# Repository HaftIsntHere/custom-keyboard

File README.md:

# Custom Keyboard
This is my fully custom keyboard, fitted with a 75% layout, 2 macro keys, a knob and an oled screen!

I made this project as a continuation for the hackpad, and I really wanted to know how building a real keyboard is, not just a macropad. This helped me finally understand how keyboards really work!
 <br>

## BOM

|Item                                                  |Quantity  |Price                                                                                   |Link #                                                                          |
|------------------------------------------------------|----------|----------------------------------------------------------------------------------------|--------------------------------------------------------------------------------|
|INDIVIDUAL ITEMS                                      |          |                                                                                        |                                                                                |
|                                                      |          |                                                                                        |                                                                                |
|Womier Coffee Cat keycaps                             |1         |26.54 USD                                                                               |https://womierkeyboard.com/products/womier-coffee-cat-143?variant=40539585740871|
|Akko V3 Creamy Purple Pro switches                    |90        |33.72 USD                                                                               |https://en.akkogear.com/product/akko-v3-creamy-purple-pro-switch                |
|PCB                                                   |5         |13 + ~15 = 28 USD (can't see shipping estimate right now, it doesnt let me cause of war)|                                                                                |
|                                                      |          |                                                                                        |                                                                                |
|ALIEXPRESS ITEMS                                      |          |                                                                                        |                                                                                |
|                                                      |          |                                                                                        |                                                                                |
|Knob                                                  |1         |3.58 USD                                                                                |https://www.aliexpress.com/item/1005007576522714.html                           |
|OLED Screen 128x32                                    |1         |3.68 USD                                                                                |https://www.aliexpress.com/item/1005007038294972.html                           |
|DO-35 Diodes                                          |100       |1.65 USD                                                                                |https://www.aliexpress.com/item/4000142272546.html                              |
|Hot swap sockets                                      |110       |15.59 USD                                                                               |https://www.aliexpress.com/item/1005007476614771.html                           |
|Stabilizers (4x 2u + 1x 6.25u)                        |4+1       |7.24 USD                                                                                |https://www.aliexpress.com/item/1005006528731543.html                           |
|ESP32 S3 Devkit C1                                    |1         |19.56 USD (including shipping)                                                          |https://www.aliexpress.com/item/1005003979778978.html                           |
|EC11 Rotary Encoder                                   |1         |1.56 USD (including shipping)                                                           |https://www.aliexpress.com/item/1975155185.html                                 |
|M3 Screws                                             |20        |2.54 USD                                                                                |https://www.aliexpress.com/item/32810872544.html                                |
|Poron strips                                          |64        |4.75 USD                                                                                |https://www.aliexpress.com/item/1005003607093794.html                           |
|                                                      |          |                                                                                        |                                                                                |
|AliExpress Total (including their discounts and stuff)| 51.33 USD|                                                                                        |                                                                                |
|                                                      |          |                                                                                        |                                                                                |
|TOTAL                                                 |          |139.59 USD                                                                              |                                                                                |

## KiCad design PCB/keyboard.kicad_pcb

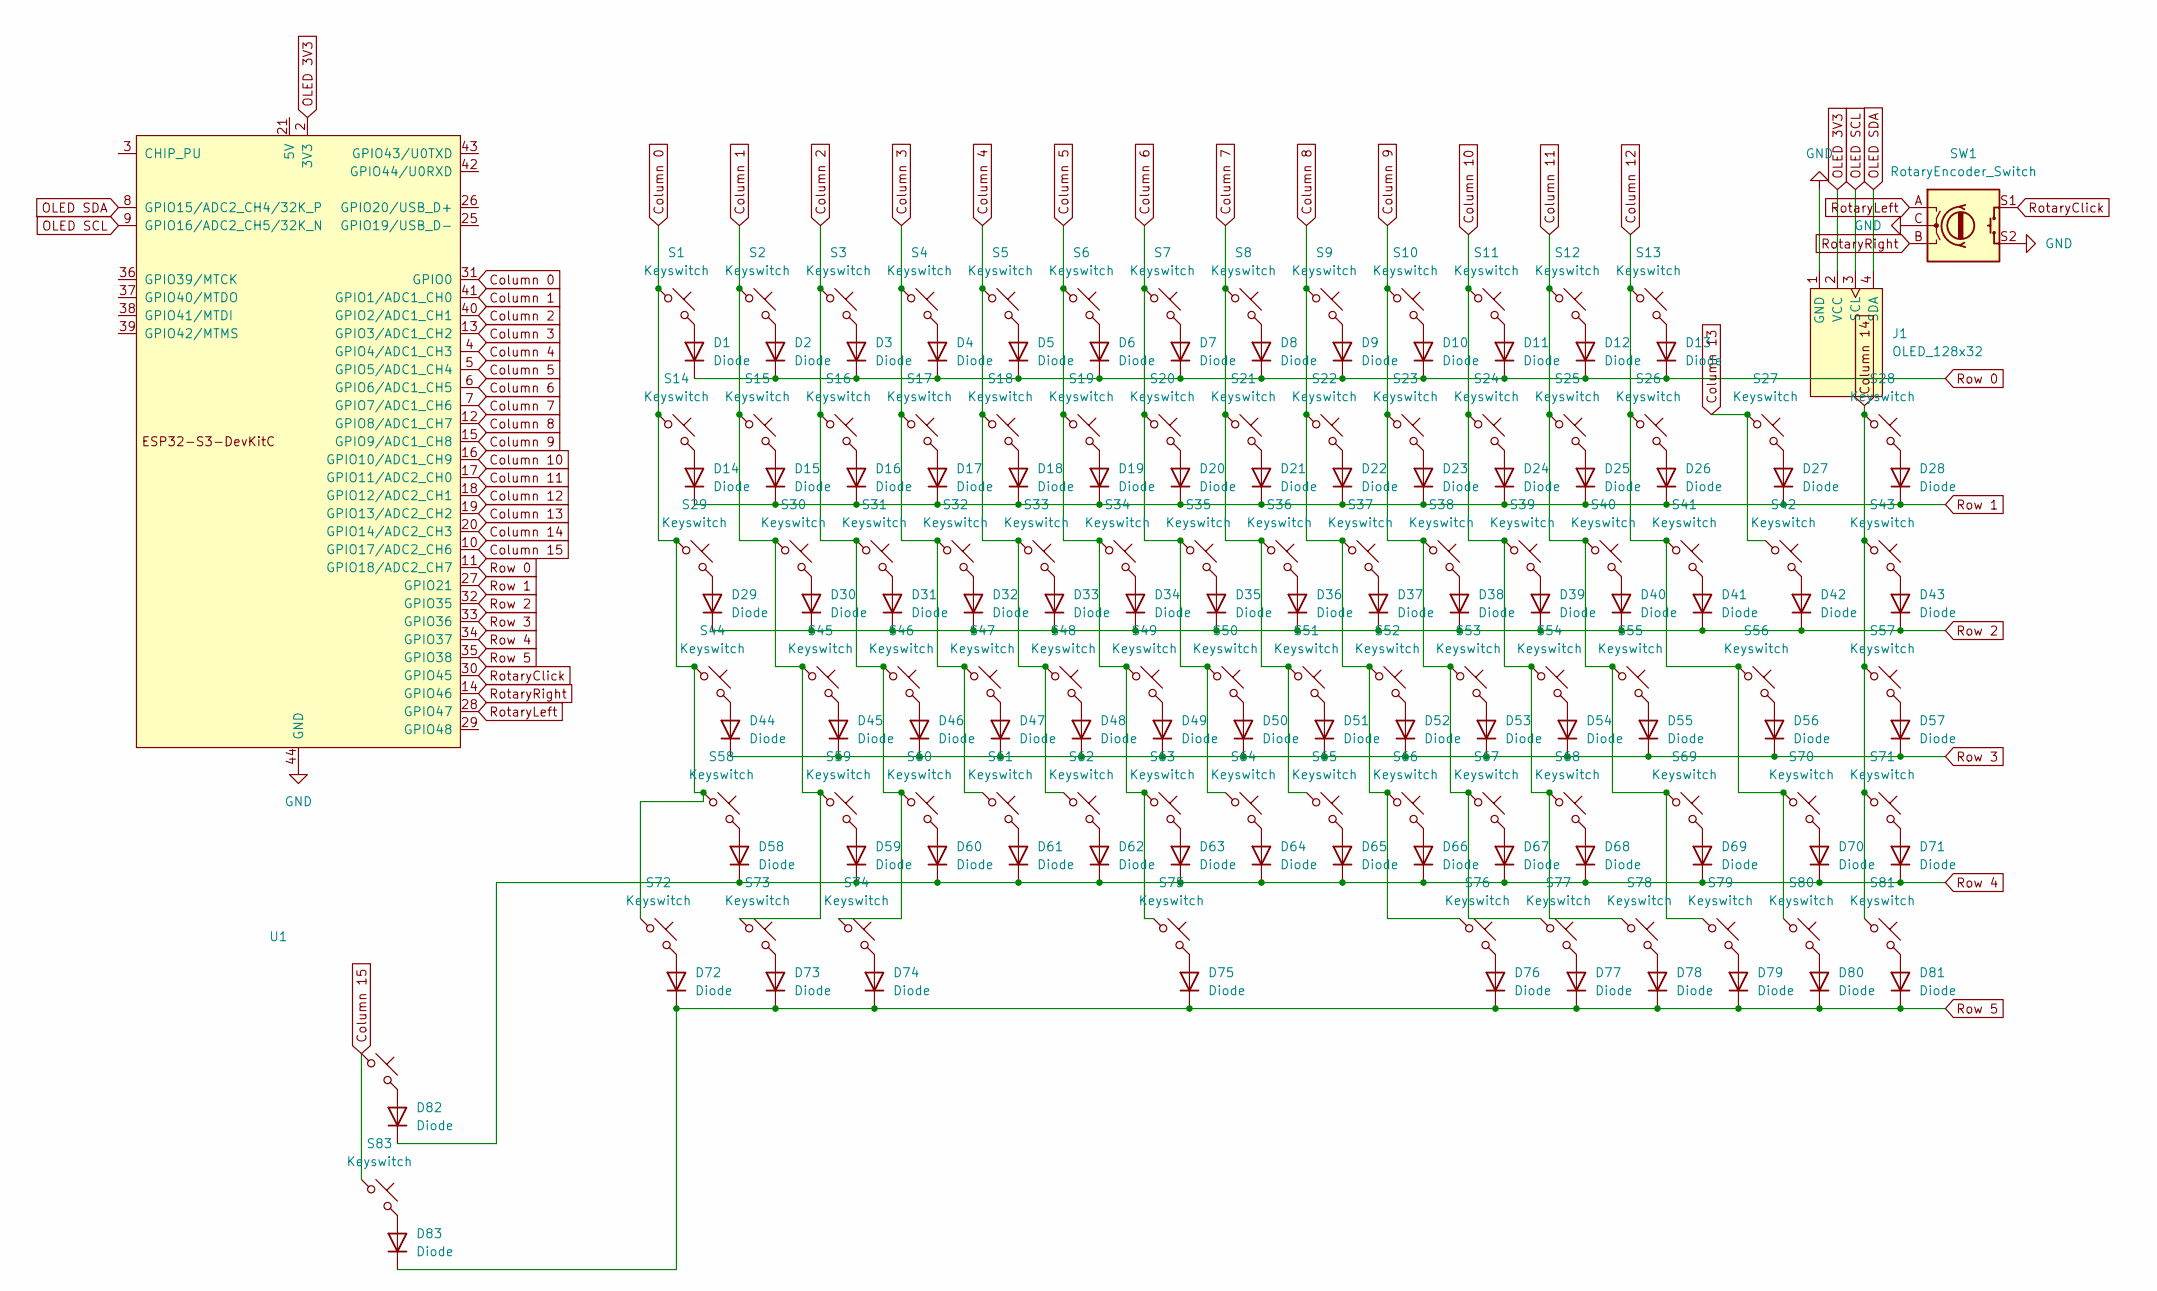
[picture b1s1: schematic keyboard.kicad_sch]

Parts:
D1, D2, D3, D4, D5, D6, D7, D8, D9, D10, D11, D12, D13, D14, D15, D16, D17, D18, D19, D20, D21, D22, D23, D24, D25, D26, D27, D28, D29, D30, D31, D32, D33, D34, D35, D36, D37, D38, D39, D40, D41, D42, D43, D44, D45, D46, D47, D48, D49, D50, D51, D52, D53, D54, D55, D56, D57, D58, D59, D60, D61, D62, D63, D64, D65, D66, D67, D68, D69, D70, D71, D72, D73, D74, D75, D76, D77, D78, D79, D80, D81, D82, D83: Diode; Diode_DO-35
J1: OLED_128x32
S1, S2, S3, S4, S5, S6, S7, S8, S9, S10, S11, S12, S13, S14, S15, S16, S17, S18, S19, S20, S21, S22, S23, S24, S25, S26, S28, S30, S31, S32, S33, S34, S35, S36, S37, S38, S39, S40, S41, S43, S45, S46, S47, S48, S49, S50, S51, S52, S53, S54, S55, S57, S59, S60, S61, S62, S63, S64, S65, S66, S67, S68, S70, S71, S76, S77, S78, S79, S80, S81, S82, S83: Keyswitch; Hotswap_MX_1.00u
S27, S58, S69: Keyswitch; Hotswap_MX_2.00u
S29, S42: Keyswitch; Hotswap_MX_1.50u
S44: Keyswitch; Hotswap_MX_1.75u
S56: Keyswitch; Hotswap_MX_2.25u
S72, S73, S74: Keyswitch; Hotswap_MX_1.25u
S75: Keyswitch; Hotswap_MX_6.25u
SW1: RotaryEncoder_Switch; RotaryEncoder_Alps_EC11E-Switch_Vertical_H20mm
U1: ESP32-S3-DevKitC

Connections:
Column 0: S1.1, S14.1, S29.1, S44.1, S58.1, S72.1, U1.31 (GPIO0)
Column 1: S2.1, S15.1, S30.1, S45.1, S59.1, S73.1, U1.41 (GPIO1/ADC1_CH0)
Column 2: S3.1, S16.1, S31.1, S46.1, S60.1, S74.1, U1.40 (GPIO2/ADC1_CH1)
Column 3: S4.1, S17.1, S32.1, S47.1, S61.1, U1.13 (GPIO3/ADC1_CH2)
Column 4: S5.1, S18.1, S33.1, S48.1, S62.1, U1.4 (GPIO4/ADC1_CH3)
Column 5: S6.1, S19.1, S34.1, S49.1, S63.1, S75.1, U1.5 (GPIO5/ADC1_CH4)
Column 6: S7.1, S20.1, S35.1, S50.1, S64.1, U1.6 (GPIO6/ADC1_CH5)
Column 7: S8.1, S21.1, S36.1, S51.1, S65.1, U1.7 (GPIO7/ADC1_CH6)
Column 8: S9.1, S22.1, S37.1, S52.1, S66.1, S76.1, U1.12 (GPIO8/ADC1_CH7)
Column 9: S10.1, S23.1, S38.1, S53.1, S67.1, S77.1, U1.15 (GPIO9/ADC1_CH8)
Column 10: S11.1, S24.1, S39.1, S54.1, S68.1, S78.1, U1.16 (GPIO10/ADC1_CH9)
Column 11: S12.1, S25.1, S40.1, S55.1, S69.1, S79.1, U1.17 (GPIO11/ADC2_CH0)
Column 12: S13.1, S26.1, S41.1, S56.1, S70.1, S80.1, U1.18 (GPIO12/ADC2_CH1)
Column 13: S27.1, S42.1, U1.19 (GPIO13/ADC2_CH2)
Column 14: S28.1, S43.1, S57.1, S71.1, S81.1, U1.20 (GPIO14/ADC2_CH3)
Column 15: S82.1, S83.1, U1.10 (GPIO17/ADC2_CH6)
GND: J1.1 (GND), SW1.C, SW1.S2, U1.22 (GND), U1.23 (GND), U1.24 (GND), U1.44 (GND)
unnamed: D1.2 (A), S1.2
unnamed: D2.2 (A), S2.2
unnamed: D3.2 (A), S3.2
unnamed: D4.2 (A), S4.2
unnamed: D5.2 (A), S5.2
unnamed: D6.2 (A), S6.2
unnamed: D7.2 (A), S7.2
unnamed: D8.2 (A), S8.2
unnamed: D9.2 (A), S9.2
unnamed: D10.2 (A), S10.2
unnamed: D11.2 (A), S11.2
unnamed: D12.2 (A), S12.2
unnamed: D13.2 (A), S13.2
unnamed: D14.2 (A), S14.2
unnamed: D15.2 (A), S15.2
unnamed: D16.2 (A), S16.2
unnamed: D17.2 (A), S17.2
unnamed: D18.2 (A), S18.2
unnamed: D19.2 (A), S19.2
unnamed: D20.2 (A), S20.2
unnamed: D21.2 (A), S21.2
unnamed: D22.2 (A), S22.2
unnamed: D23.2 (A), S23.2
unnamed: D24.2 (A), S24.2
unnamed: D25.2 (A), S25.2
unnamed: D26.2 (A), S26.2
unnamed: D27.2 (A), S27.2
unnamed: D28.2 (A), S28.2
unnamed: D29.2 (A), S29.2
unnamed: D30.2 (A), S30.2
unnamed: D31.2 (A), S31.2
unnamed: D32.2 (A), S32.2
unnamed: D33.2 (A), S33.2
unnamed: D34.2 (A), S34.2
unnamed: D35.2 (A), S35.2
unnamed: D36.2 (A), S36.2
unnamed: D37.2 (A), S37.2
unnamed: D38.2 (A), S38.2
unnamed: D39.2 (A), S39.2
unnamed: D40.2 (A), S40.2
unnamed: D41.2 (A), S41.2
unnamed: D42.2 (A), S42.2
unnamed: D43.2 (A), S43.2
unnamed: D44.2 (A), S44.2
unnamed: D45.2 (A), S45.2
unnamed: D46.2 (A), S46.2
unnamed: D47.2 (A), S47.2
unnamed: D48.2 (A), S48.2
unnamed: D49.2 (A), S49.2
unnamed: D50.2 (A), S50.2
unnamed: D51.2 (A), S51.2
unnamed: D52.2 (A), S52.2
unnamed: D53.2 (A), S53.2
unnamed: D54.2 (A), S54.2
unnamed: D55.2 (A), S55.2
unnamed: D56.2 (A), S56.2
unnamed: D57.2 (A), S57.2
unnamed: D58.2 (A), S58.2
unnamed: D59.2 (A), S59.2
unnamed: D60.2 (A), S60.2
unnamed: D61.2 (A), S61.2
unnamed: D62.2 (A), S62.2
unnamed: D63.2 (A), S63.2
unnamed: D64.2 (A), S64.2
unnamed: D65.2 (A), S65.2
unnamed: D66.2 (A), S66.2
unnamed: D67.2 (A), S67.2
unnamed: D68.2 (A), S68.2
unnamed: D69.2 (A), S69.2
unnamed: D70.2 (A), S70.2
unnamed: D71.2 (A), S71.2
unnamed: D72.2 (A), S72.2
unnamed: D73.2 (A), S73.2
unnamed: D74.2 (A), S74.2
unnamed: D75.2 (A), S75.2
unnamed: D76.2 (A), S76.2
unnamed: D77.2 (A), S77.2
unnamed: D78.2 (A), S78.2
unnamed: D79.2 (A), S79.2
unnamed: D80.2 (A), S80.2
unnamed: D81.2 (A), S81.2
unnamed: D82.2 (A), S82.2
unnamed: D83.2 (A), S83.2
OLED 3V3: J1.2 (VCC), U1.1 (3V3), U1.2 (3V3)
OLED SCL: J1.3 (SCL), U1.9 (GPIO16/ADC2_CH5/32K_N)
OLED SDA: J1.4 (SDA), U1.8 (GPIO15/ADC2_CH4/32K_P)
RotaryClick: SW1.S1, U1.30 (GPIO45)
RotaryLeft: SW1.A, U1.28 (GPIO47)
RotaryRight: SW1.B, U1.14 (GPIO46)
Row 0: D1.1 (K), D2.1 (K), D3.1 (K), D4.1 (K), D5.1 (K), D6.1 (K), D7.1 (K), D8.1 (K), D9.1 (K), D10.1 (K), D11.1 (K), D12.1 (K), D13.1 (K), U1.11 (GPIO18/ADC2_CH7)
Row 1: D14.1 (K), D15.1 (K), D16.1 (K), D17.1 (K), D18.1 (K), D19.1 (K), D20.1 (K), D21.1 (K), D22.1 (K), D23.1 (K), D24.1 (K), D25.1 (K), D26.1 (K), D27.1 (K), D28.1 (K), U1.27 (GPIO21)
Row 2: D29.1 (K), D30.1 (K), D31.1 (K), D32.1 (K), D33.1 (K), D34.1 (K), D35.1 (K), D36.1 (K), D37.1 (K), D38.1 (K), D39.1 (K), D40.1 (K), D41.1 (K), D42.1 (K), D43.1 (K), U1.32 (GPIO35)
Row 3: D44.1 (K), D45.1 (K), D46.1 (K), D47.1 (K), D48.1 (K), D49.1 (K), D50.1 (K), D51.1 (K), D52.1 (K), D53.1 (K), D54.1 (K), D55.1 (K), D56.1 (K), D57.1 (K), U1.33 (GPIO36)
Row 4: D58.1 (K), D59.1 (K), D60.1 (K), D61.1 (K), D62.1 (K), D63.1 (K), D64.1 (K), D65.1 (K), D66.1 (K), D67.1 (K), D68.1 (K), D69.1 (K), D70.1 (K), D71.1 (K), D82.1 (K), U1.34 (GPIO37)
Row 5: D72.1 (K), D73.1 (K), D74.1 (K), D75.1 (K), D76.1 (K), D77.1 (K), D78.1 (K), D79.1 (K), D80.1 (K), D81.1 (K), D83.1 (K), U1.35 (GPIO38)

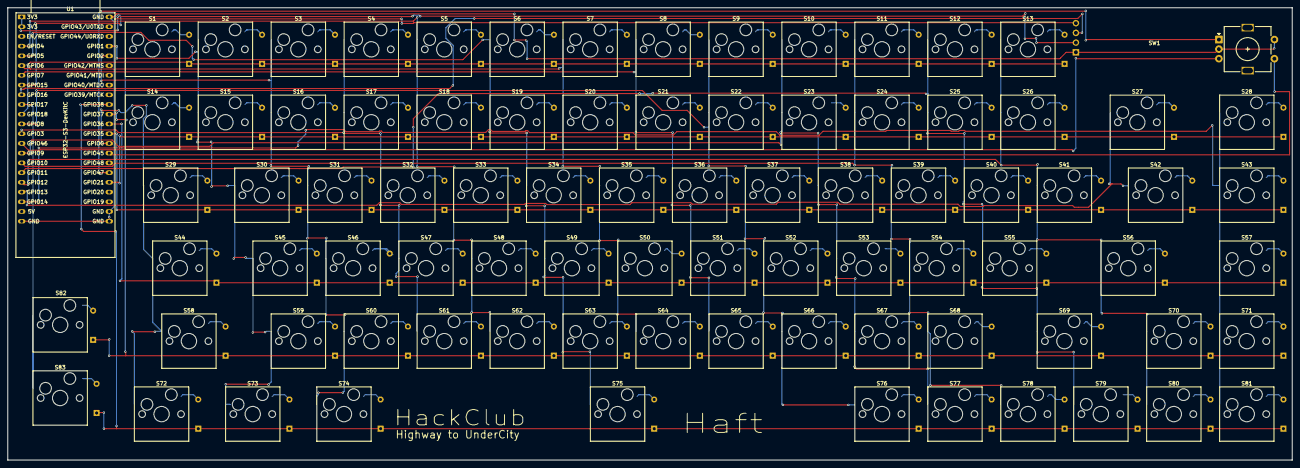
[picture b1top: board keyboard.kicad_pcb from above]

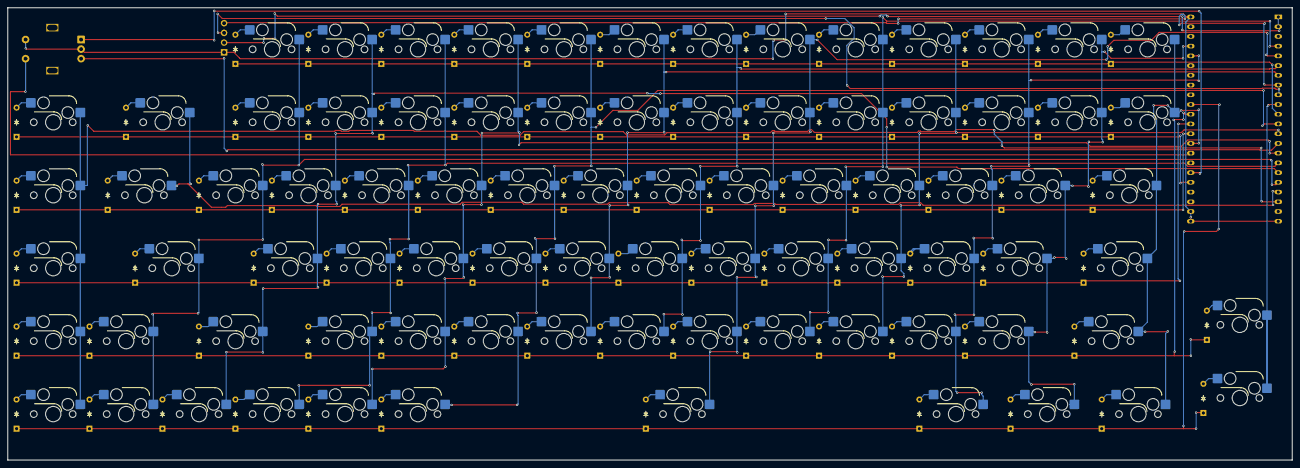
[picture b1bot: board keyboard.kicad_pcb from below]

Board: 2 copper layers, 335.4 x 118.1 mm, 169 parts (83 on the bottom side), 112 nets.

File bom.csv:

Designator,Footprint,Quantity,Value,LCSC Part #
"D1, D2, D3, D4, D5, D6, D7, D8, D9, D10...D83",Diode_DO-35,83,Diode,
J1,OLED_128x32,1,OLED_128x32,
"S1, S2, S3, S4, S5, S6, S7, S8, S9, S10...",Hotswap_MX_1.00u,72,Keyswitch,
"S27, S58, S69",Hotswap_MX_2.00u,3,Keyswitch,
"S29, S42",Hotswap_MX_1.50u,2,Keyswitch,
S44,Hotswap_MX_1.75u,1,Keyswitch,
S56,Hotswap_MX_2.25u,1,Keyswitch,
"S72, S73, S74",Hotswap_MX_1.25u,3,Keyswitch,
S75,Hotswap_MX_6.25u,1,Keyswitch,
SW1,RotaryEncoder_Alps_EC11E-Switch_Vertical_H20mm,1,RotaryEncoder_Switch,
U1,ESP32-S3-DevKitC,1,ESP32-S3-DevKitC,

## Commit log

2025-06-20 LOG 1
2025-06-20 temporary
2025-06-20 Add PCB files from KiCAD
2025-06-20 add production files and gerbers generated
2025-06-21 June 21st journal entry
2025-06-22 June 22nd devlog part 1
2025-06-22 June 22nd part 2
2025-06-22 add total time today thingy
2025-06-22 update gerbers
2025-06-22 Add kicad files
2025-06-23 June 23rd entry
2025-06-23 Move BOM and make it more readable
2025-06-23 Create CAD
2025-06-23 Create s
2025-06-23 add total time thingy
2025-06-23 add CAD
2025-06-23 update keyboard with new color
2025-06-23 add stabilizers to bom
2025-07-04 fix full assembly pic
2025-07-30 Devlog July 30th
2025-09-17 Update journal with parts arrival and build progress
